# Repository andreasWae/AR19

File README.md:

# AR19
Repository inntil videre

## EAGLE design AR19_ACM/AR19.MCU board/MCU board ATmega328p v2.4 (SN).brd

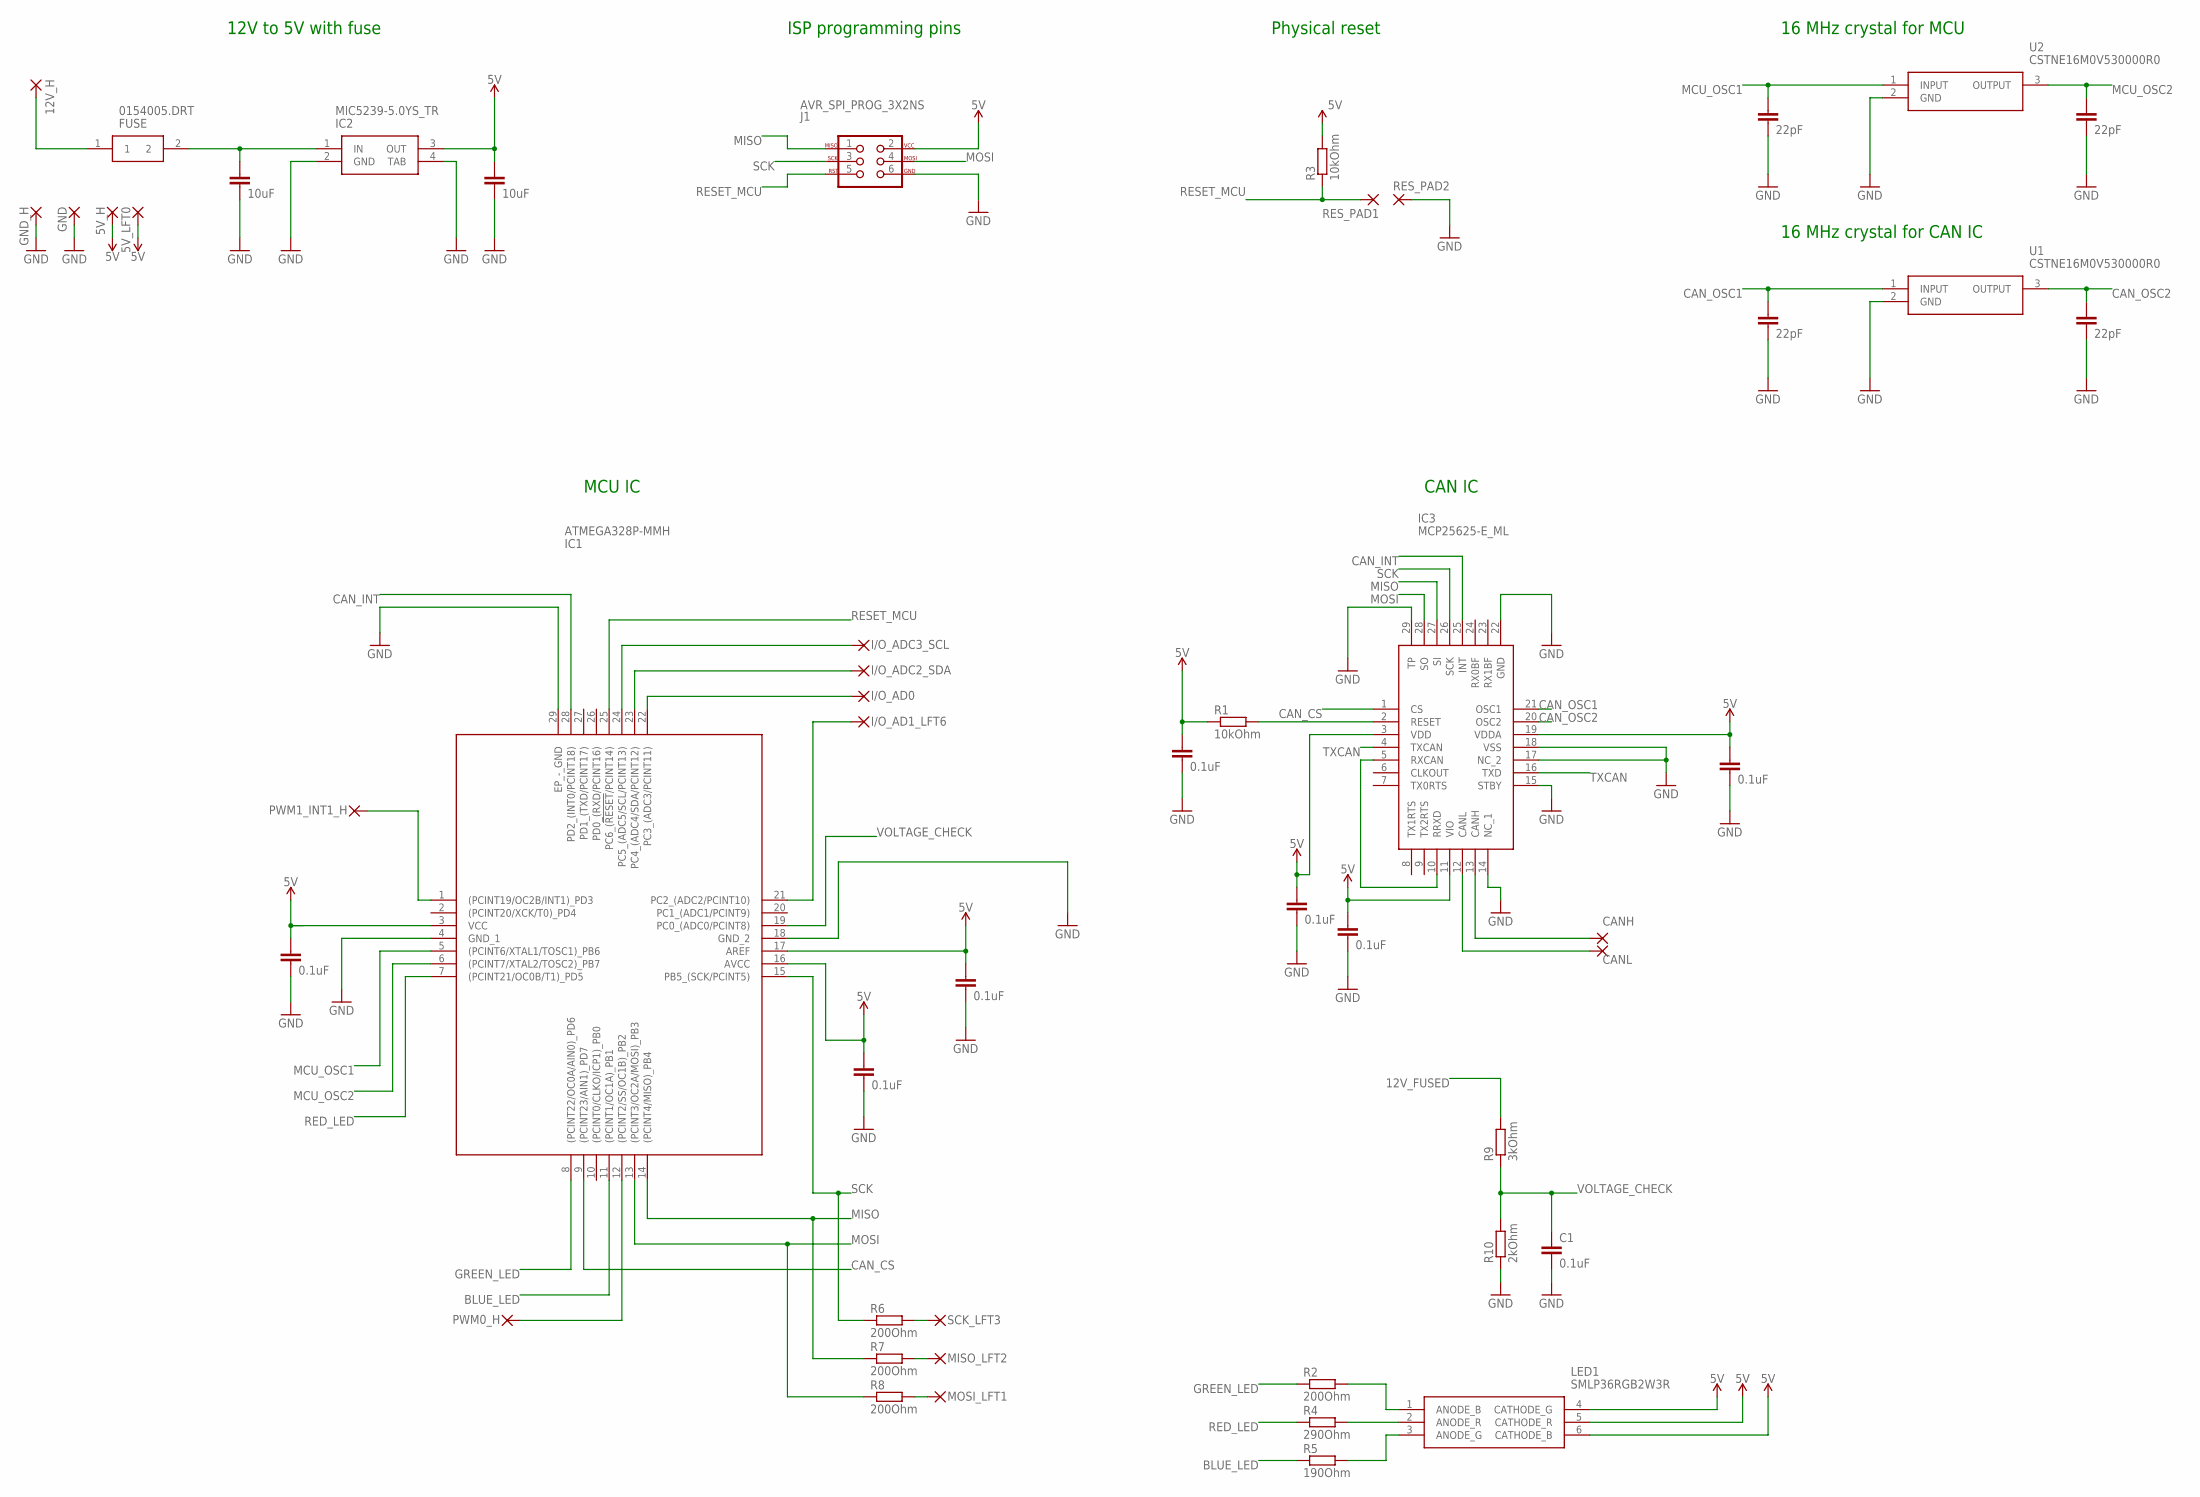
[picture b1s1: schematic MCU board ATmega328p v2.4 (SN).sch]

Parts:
5V: 5V_H; 2,15/1,0
5V1: 5V_LFT0; 2,15/1,0
12V_H: 12V; 2,15/1,0
C1, C6, C7, C8, C12, C13, C16, C17: 0.1uF; C0603
C2, C3, C5, C9: 22pF; C0603
C10, C11: 10uF; C0603
CANH: I/O_CANH_H; 2,15/1,0
CANL: I/O_CANH_H; 2,15/1,0
FUSE: 0154005.DRT; 0154001.DRT
GND: GND_H; 2,15/1,0
GND30_H: GND; 2,15/1,0
I/O_AD0: I/O_AD0_LFT7; 2,15/1,0
I/O_AD1: I/O_AD1_LFT6; 2,15/1,0
I/O_ADC2_SDA: I/O_ADC2_SDA_LFT5; 2,15/1,0
I/O_ADC3_SCL: I/O_ADC3_SCL_LFT4; 2,15/1,0
IC1: ATMEGA328P-MMH; QFN45P400X400X100-29N
IC2: MIC5239-5.0YS_TR; SOT230P700X170-4N
IC3: MCP25625-E_ML; QFN65P600X600X100-29N
J1: AVR_SPI_PROG_3X2NS; 2X3-NS
LED1: SMLP36RGB2W3R; ROHM-1510-(0604)
MISO: MISO_LFT2; 2,15/1,0
MOSI: MOSI_LFT1; 2,15/1,0
PWM0_H: PWM0; 2,15/1,0
PWM1_INT1_H: PWM0_INT; 2,15/1,0
R1, R3: 10kOhm; R0603
R2, R6, R7, R8: 200Ohm; R0603
R4: 290Ohm; R0603
R5: 190Ohm; R0603
R9: 3kOhm; R0603
R10: 2kOhm; R0603
RES_PAD1: RES_PAD; SMD1,27-2,54
RES_PAD2: RES_PAD2; SMD1,27-2,54
SCK: SCK_LFT3; 2,15/1,0
U1, U2: CSTNE16M0V530000R0

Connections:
5V: 5V.1, 5V1.1, C6.1, C7.1, C8.1, C11.1, C12.1, C13.1, C16.1, C17.1, IC1.3 (VCC), IC1.16 (AVCC), IC1.17 (AREF), IC2.3 (OUT), IC3.3 (VDD), IC3.11 (VIO), IC3.19 (VDDA), J1.2, LED1.4 (CATHODE_G), LED1.5 (CATHODE_R), LED1.6 (CATHODE_B), R1.1, R3.2
12V_FUSED: C10.1, FUSE.2, IC2.1 (IN), R9.2
12V_UNFUSED: 12V_H.1, FUSE.1
BLUE_LED: IC1.11 ((PCINT1/OC1A)_PB1), R5.1
CANH: CANH.1, IC3.13 (CANH)
CANL: CANL.1, IC3.12 (CANL)
CAN_CS: IC1.9 ((PCINT23/AIN1)_PD7), IC3.1 (CS)
CAN_INT: IC1.28 (PD2_(INT0/PCINT18)), IC3.25 (INT)
CAN_OSC1: C5.1, IC3.21 (OSC1), U1.1 (INPUT)
CAN_OSC2: C2.1, IC3.20 (OSC2), U1.3 (OUTPUT)
GND: C1.2, C2.2, C3.2, C5.2, C6.2, C7.2, C8.2, C9.2, C10.2, C11.2, C12.2, C13.2, C16.2, C17.2, GND.1, GND30_H.1, IC1.4 (GND_1), IC1.18 (GND_2), IC1.29 (EP_-_GND), IC2.2 (GND), IC2.4 (TAB), IC3.14 (NC_1), IC3.15 (STBY), IC3.17 (NC_2), IC3.18 (VSS), IC3.22 (GND), IC3.29 (TP), J1.6, R10.1, RES_PAD2.1, U1.2 (GND), U2.2 (GND)
GREEN_LED: IC1.8 ((PCINT22/OC0A/AIN0)_PD6), R2.1
I/OAD0: I/O_AD0.1, IC1.22 (PC3_(ADC3/PCINT11))
I/OADC2: I/O_ADC2_SDA.1, IC1.23 (PC4_(ADC4/SDA/PCINT12))
I/O_ADC3: I/O_ADC3_SCL.1, IC1.24 (PC5_(ADC5/SCL/PCINT13))
I/O_D2_INT: IC1.1 ((PCINT19/OC2B/INT1)_PD3), PWM1_INT1_H.1
MCU_OSC1: C3.1, IC1.5 ((PCINT6/XTAL1/TOSC1)_PB6), U2.1 (INPUT)
MCU_OSC2: C9.1, IC1.6 ((PCINT7/XTAL2/TOSC2)_PB7), U2.3 (OUTPUT)
MISO: IC1.14 ((PCINT4/MISO)_PB4), IC3.27 (SI), J1.1, R7.1
MOSI: IC1.13 ((PCINT3/OC2A/MOSI)_PB3), IC3.28 (SO), J1.4, R8.1
unnamed: IC3.2 (RESET), R1.2
unnamed: IC1.12 ((PCINT2/SS/OC1B)_PB2), PWM0_H.1
unnamed: I/O_AD1.1, IC1.21 (PC2_(ADC2/PCINT10))
unnamed: LED1.1 (ANODE_B), R2.2
unnamed: LED1.2 (ANODE_R), R4.2
unnamed: LED1.3 (ANODE_G), R5.2
unnamed: R6.2, SCK.1
unnamed: MISO.1, R7.2
unnamed: MOSI.1, R8.2
RED_LED: IC1.7 ((PCINT21/OC0B/T1)_PD5), R4.1
RESET_MCU: IC1.25 (PC6_(!RESET!/PCINT14)), J1.5, R3.1, RES_PAD1.1
RXCAN: IC3.5 (RXCAN), IC3.10 (RRXD)
SCK: IC1.15 (PB5_(SCK/PCINT5)), IC3.26 (SCK), J1.3, R6.1
TXCAN: IC3.4 (TXCAN), IC3.16 (TXD)
VOLTAGE_CHECK: C1.1, IC1.19 (PC0_(ADC0/PCINT8)), R9.1, R10.2

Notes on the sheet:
12V to 5V with fuse
ISP programming pins
Physical reset
16 MHz crystal for MCU
16 MHz crystal for CAN IC
CAN IC
MCU IC

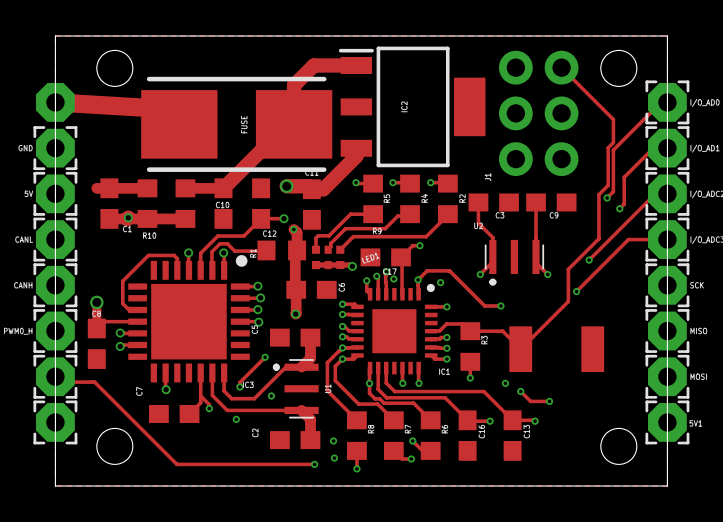
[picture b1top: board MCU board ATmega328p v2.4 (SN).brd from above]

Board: 4 copper layers, 34.0 x 25.0 mm, 50 parts (1 on the bottom side), 35 nets.

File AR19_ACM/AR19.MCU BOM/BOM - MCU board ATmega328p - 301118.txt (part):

Partlist exported from C:/Users/Nylund/Documents/Align Racing/AR19/PCB_Designs/GitKraken/AR19/ACM - Align CAN-bus Module/AR19.MCU board/MCU board ATmega328p v2.4.sch at 30-Nov-18 16:28

Part          Value              Device             Package               Description                                                                                                                                       ALLIED_NUMBER ALLIED_PRICE-STOCK                                                         ARROW_PART_NUMBER  ARROW_PRICE-STOCK                                                         DESCRIPTION                                                                                                                                       HEIGHT MANUFACTURER_NAME  MANUFACTURER_PART_NUMBER RS_PART_NUMBER RS_PRICE-STOCK                                  SPICEMODEL SPICEPREFIX
12V           12V                2,54/1,0           2,54/1,0              THROUGH-HOLE PAD                                                                                                                                                                                                                                                                                                                                                                                                                                                                                                                                                                                                                  
C1            0.1uF              CC0603             C0603                 CAPACITOR, European symbol                                                                                                                                                                                                                                                                                                                                                                                                                                                                                                                                                                                  NONE       C          
C2            22pF               CC0603             C0603                 CAPACITOR, European symbol                                                                                                                                                                                                                                                                                                                                                                                                                                                                                                                                                                                  NONE       C          
C3            22pF               CC0603             C0603                 CAPACITOR, European symbol                                                                                                                                                                                                                                                                                                                                                                                                                                                                                                                                                                                  NONE       C          
C5            22pF               CC0603             C0603                 CAPACITOR, European symbol                                                                                                                                                                                                                                                                                                                                                                                                                                                                                                                                                                                  NONE       C          
C6            0.1uF              CC0603             C0603                 CAPACITOR, European symbol                                                                                                                                                                                                                                                                                                                                                                                                                                                                                                                                                                                  NONE       C          
C7            0.1uF              CC0603             C0603                 CAPACITOR, European symbol                                                                                                                                                                                                                                                                                                                                                                                                                                                                                                                                                                                  NONE       C          
C8            0.1uF              CC0603             C0603                 CAPACITOR, European symbol                                                                                                                                                                                                                                                                                                                                                                                                                                                                                                                                                                                  NONE       C          
C9            22pF               CC0603             C0603                 CAPACITOR, European symbol                                                                                                                                                                                                                                                                                                                                                                                                                                                                                                                                                                                  NONE       C          
C10           10uF               CC0603             C0603                 CAPACITOR, European symbol                                                                                                                                                                                                                                                                                                                                                                                                                                                                                                                                                                                  NONE       C          
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
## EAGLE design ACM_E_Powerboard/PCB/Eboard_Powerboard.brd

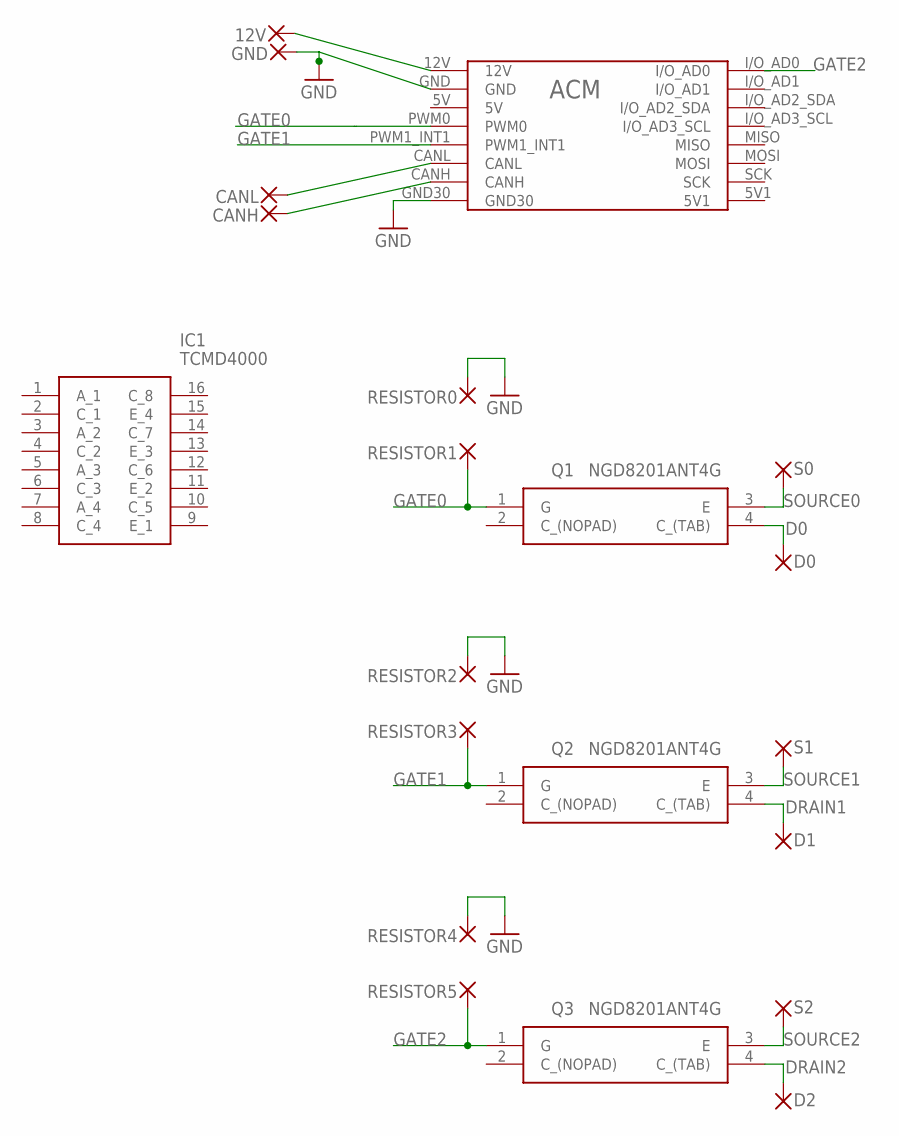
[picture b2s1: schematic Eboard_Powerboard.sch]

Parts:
12V: 2,15/1,0
CANH: 2,15/1,0
CANL: 2,15/1,0
D0, D1, D2: 2,54/1,0
GND: 2,15/1,0
IC1: TCMD4000; SOIC127P695X210-16N
Q1, Q2, Q3: NGD8201ANT4G; TO229P990X238-4N
RESISTOR0, RESISTOR1, RESISTOR2, RESISTOR3, RESISTOR4, RESISTOR5: 2,15/1,0
S0, S1, S2: 2,54/1,0
U$1: ACM_CASTELLATED; ACM_CAS_FP

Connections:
D0: D0.1, Q1.4 (C_(TAB))
DRAIN1: D1.1, Q2.4 (C_(TAB))
DRAIN2: D2.1, Q3.4 (C_(TAB))
GATE0: Q1.1 (G), RESISTOR1.1, U$1.PWM0
GATE1: Q2.1 (G), RESISTOR3.1, U$1.PWM1_INT1
GATE2: Q3.1 (G), RESISTOR5.1, U$1.I/O_AD0
GND: GND.1, RESISTOR0.1, RESISTOR2.1, RESISTOR4.1, U$1.GND, U$1.GND30
unnamed: 12V.1, U$1.12V
unnamed: CANL.1, U$1.CANL
unnamed: CANH.1, U$1.CANH
SOURCE0: Q1.3 (E), S0.1
SOURCE1: Q2.3 (E), S1.1
SOURCE2: Q3.3 (E), S2.1

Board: 2 copper layers, 21 parts (2 on the bottom side), 13 nets, no tracks yet.

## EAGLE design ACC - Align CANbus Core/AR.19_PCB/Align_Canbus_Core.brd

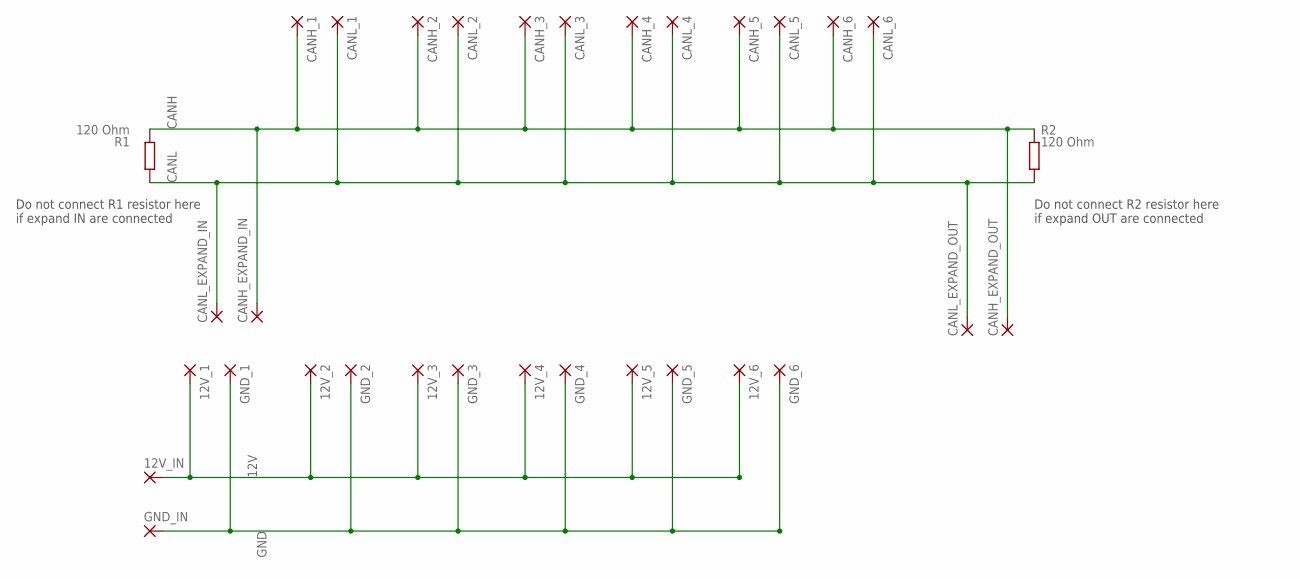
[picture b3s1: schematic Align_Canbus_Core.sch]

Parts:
12V_1, 12V_2, 12V_3, 12V_4, 12V_5, 12V_6: 2,15/1,0
12V_IN: 3,81/1,4
CANH_1, CANH_2, CANH_3, CANH_4, CANH_5, CANH_6: 2,15/1,0
CANH_EXPAND_IN: 2,54/1,0
CANH_EXPAND_OUT: 2,54/1,0
CANL_1, CANL_2, CANL_3, CANL_4, CANL_5, CANL_6: 2,15/1,0
CANL_EXPAND_IN: 2,54/1,0
CANL_EXPAND_OUT: 2,54/1,0
GND_1, GND_2, GND_3, GND_4, GND_5, GND_6: 2,15/1,0
GND_IN: 3,81/1,4
R1, R2: 120 Ohm; R0603

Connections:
12V: 12V_6.1, 12V_IN.1
CANH: CANH_1.1, CANH_2.1, CANH_3.1, CANH_4.1, CANH_5.1, CANH_6.1, CANH_EXPAND_IN.1, CANH_EXPAND_OUT.1, R1.2, R2.1
CANH1: 12V_1.1, 12V_2.1, 12V_3.1, 12V_5.1
CANL: CANL_1.1, CANL_2.1, CANL_3.1, CANL_4.1, CANL_5.1, CANL_6.1, CANL_EXPAND_IN.1, CANL_EXPAND_OUT.1, R1.1, R2.2
CANL1: GND_1.1, GND_2.1, GND_3.1, GND_5.1
GND: GND_6.1, GND_IN.1

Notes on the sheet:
Do not connect R1 resistor here if expand IN are connected
Do not connect R2 resistor here if expand OUT are connected

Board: 2 copper layers, 32 parts (0 on the bottom side), 6 nets, no tracks yet.

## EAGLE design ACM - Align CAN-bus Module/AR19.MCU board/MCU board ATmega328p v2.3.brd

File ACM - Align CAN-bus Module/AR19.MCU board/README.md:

# PCB Board
## Layers:
- Top Layer: 5V + Signal
- Route #2 Layer: Signal 1
- Route #3 Layer: Signal 2
- Route #4 Layer: GND

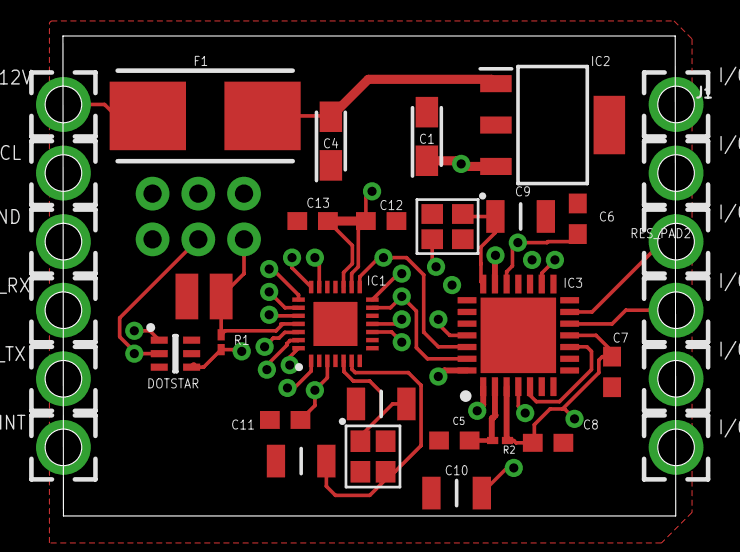
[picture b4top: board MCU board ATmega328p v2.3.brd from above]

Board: 4 copper layers, 34.0 x 26.7 mm, 37 parts (0 on the bottom side), 28 nets.

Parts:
12V: 2,54/2,0(HALFHOLE)H+V
C1, C4: 10uF; CAPPM3216X180N
C2, C3, C9, C10: 22pF; CAPC3216X229N
C5, C6, C7, C8, C11, C12, C13: 0.1uF; C0603
DOTSTAR: COM-14608; SON75P200X200X100-6N
F1: 0154005.DRT; 0154001.DRT
GND: 2,54/2,0(HALFHOLE)H+V
I/O_AD1, I/O_AD2, I/O_AD3, I/O_AD4_SDA, I/O_AD5_SCL: 2,54/2,0(HALFHOLE)H+V
I/O_CANH: 2,54/2,0(HALFHOLE)H+V
I/O_CANL: 2,54/2,0(HALFHOLE)H+V
I/O_D0_RX, I/O_D1_TX, I/O_D2_INT: 2,54/2,0(HALFHOLE)H+V
IC1: ATMEGA328P-MMH; QFN45P400X400X100-29N
IC2: MIC5239-5.0YS_TR; SOT230P700X170-4N
IC3: MCP25625-E_ML; QFN65P600X600X100-29N
J1: AVR_SPI_PROG_3X2NS; 2X3-NS
R1, R2: 10KΩ; RESC0603X28N
RES_PAD1, RES_PAD2: SMD1,27-2,54
U$1, U$2: FA-20H

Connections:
5V: C1.1, C6.1, C7.1, C8.1, C11.1, C12.1, C13.1, DOTSTAR.4, IC1.3, IC1.16, IC1.17, IC2.3, IC3.3, IC3.11, IC3.19, J1.2, R1.2, R2.2
12V_FUSED: C4.2, F1.2, IC2.1
12V_UNFUSED: 12V.P$1, F1.1
CANH: I/O_CANH.P$1, IC3.13
CANL: I/O_CANL.P$1, IC3.12
CAN_CS: IC1.11, IC3.1
CAN_INIT: IC1.28, IC3.25
CAN_OSC1: C9.2, IC3.21, U$1.1
CAN_OSC2: C10.2, IC3.20, U$1.3
DOTS_CS: DOTSTAR.1, IC1.10
GND: C1.2, C2.1, C3.1, C4.1, C5.2, C6.2, C7.2, C8.2, C9.1, C10.1, C11.2, C12.2, C13.2, DOTSTAR.3, GND.P$1, IC1.4, IC1.18, IC1.29, IC2.2, IC2.4, IC3.14, IC3.15, IC3.17, IC3.18, IC3.22, J1.6, RES_PAD2.1
I/O_AD1: I/O_AD1.P$1, IC1.20
I/O_AD2: I/O_AD2.P$1, IC1.21
I/O_AD3: I/O_AD3.P$1, IC1.22
I/O_AD4_SCL: I/O_AD4_SDA.P$1, IC1.23
I/O_AD5_SCL: I/O_AD5_SCL.P$1, IC1.24
I/O_D0_RX: I/O_D0_RX.P$1, IC1.26
I/O_D1_TX: I/O_D1_TX.P$1, IC1.27
I/O_D2_INT: I/O_D2_INT.P$1, IC1.1
MCP_RESET: C5.1, IC3.2, R2.1
MCU_OSC1: C2.2, IC1.5, U$2.1
MCU_OSC2: C3.2, IC1.6, U$2.3
MISO: IC1.14, IC3.28, J1.1
MOSI: IC1.13, IC3.27, J1.4
RESET_MCU: IC1.25, J1.5, R1.1, RES_PAD1.1
RXCAN: IC3.5, IC3.10
SCK: DOTSTAR.2, IC1.15, IC3.26, J1.3
TXCAN: IC3.4, IC3.16

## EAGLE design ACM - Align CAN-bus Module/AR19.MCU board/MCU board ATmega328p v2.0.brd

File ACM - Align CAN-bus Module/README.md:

# ACM - Align CAN-bus Module
TBA

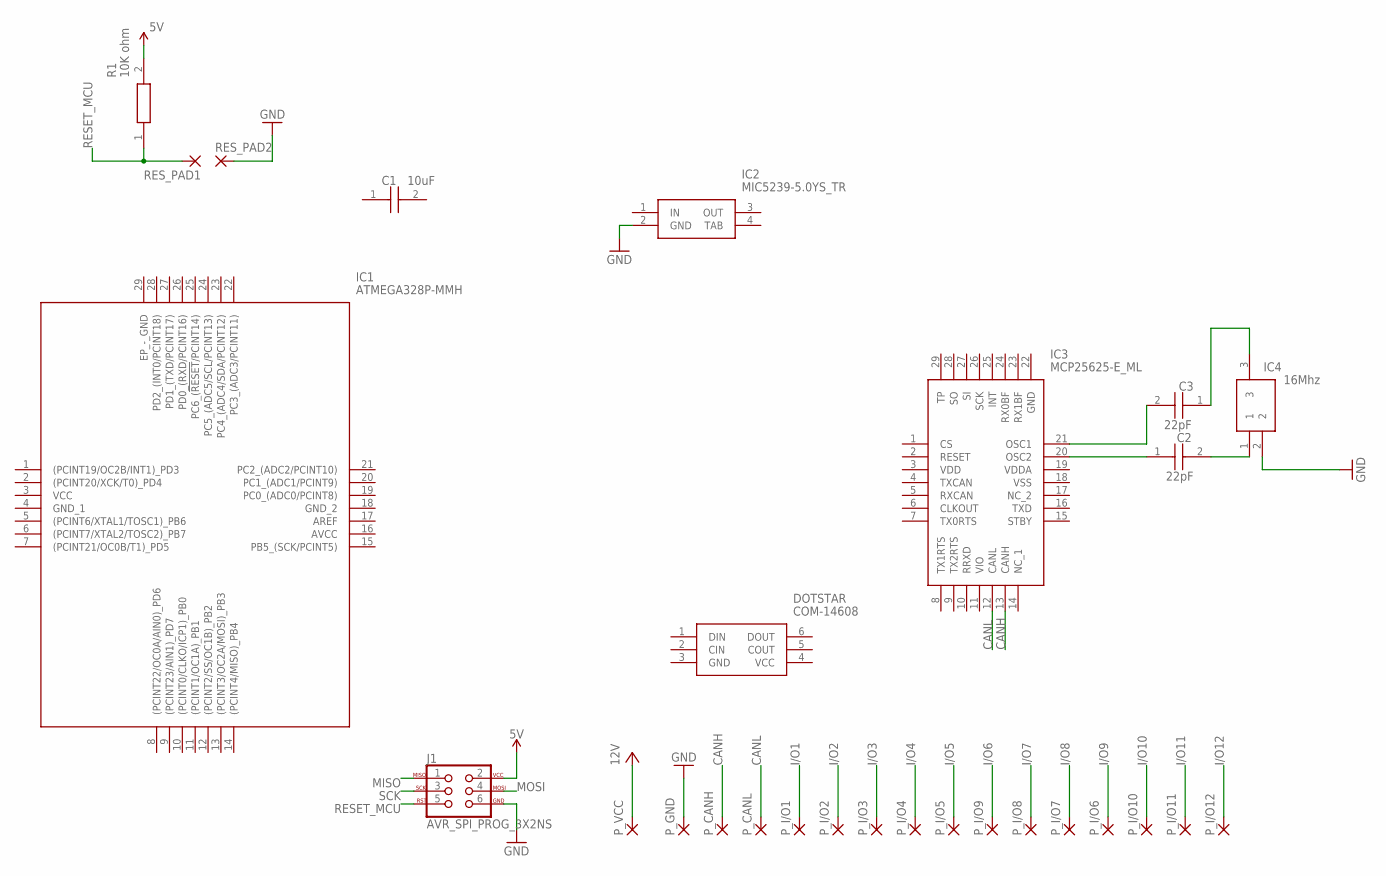
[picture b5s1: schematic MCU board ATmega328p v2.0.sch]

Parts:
C1: 10uF; CAPPM3216X180N
C2, C3: 22pF; CAPC3216X229N
DOTSTAR: COM-14608; SON75P200X200X100-6N
IC1: ATMEGA328P-MMH; QFN45P400X400X100-29N
IC2: MIC5239-5.0YS_TR; SOT230P700X170-4N
IC3: MCP25625-E_ML; QFN65P600X600X100-29N
IC4: 16Mhz; CSTCE16M0V13C99R0
J1: AVR_SPI_PROG_3X2NS; 2X3-NS
P_CANH: 2,15/1,0
P_CANL: 2,15/1,0
P_GND: 2,15/1,0
P_I/O1, P_I/O2, P_I/O3, P_I/O4, P_I/O5, P_I/O6, P_I/O7, P_I/O8, P_I/O9, P_I/O10, P_I/O11, P_I/O12: 2,15/1,0
P_VCC: 2,15/1,0
R1: 10K ohm; RESC0603X28N
RES_PAD1, RES_PAD2: SMD2; SMD1,27-2,54

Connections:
5V: J1.2, R1.2
CANH: IC3.13 (CANH), P_CANH.1
CANL: IC3.12 (CANL), P_CANL.1
GND: IC2.2 (GND), IC3.22 (GND), IC4.2, J1.6, P_GND.1, RES_PAD2.1
I/O1: P_I/O1.1
I/O2: P_I/O2.1
I/O3: P_I/O3.1
I/O4: P_I/O4.1
I/O5: P_I/O5.1
I/O6: P_I/O9.1
I/O7: P_I/O8.1
I/O8: P_I/O7.1
I/O9: P_I/O6.1
I/O10: P_I/O10.1
I/O11: P_I/O11.1
I/O12: P_I/O12.1
MISO: J1.1
MOSI: J1.4
unnamed: C3.2, IC4.1
unnamed: C3.1, IC3.20 (OSC2)
unnamed: C2.2, IC3.21 (OSC1)
unnamed: C2.1, IC4.3
RESET_MCU: J1.5, R1.1, RES_PAD1.1
SCK: J1.3
VCC: P_VCC.1
VDD: IC3.3 (VDD)
VDDA: IC3.19 (VDDA)
VSS: IC3.18 (VSS)

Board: 2 copper layers, 28 parts (0 on the bottom side), 9 nets, no tracks yet.

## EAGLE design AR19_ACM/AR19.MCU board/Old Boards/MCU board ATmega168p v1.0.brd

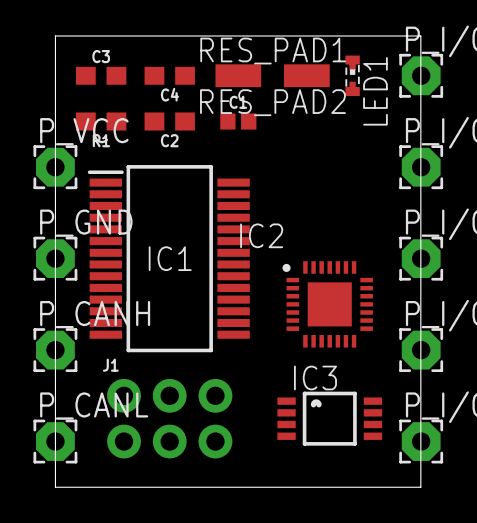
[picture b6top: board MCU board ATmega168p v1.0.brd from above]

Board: 2 copper layers, 20.3 x 25.1 mm, 21 parts (0 on the bottom side), 13 nets, no tracks yet.

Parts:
C1: 0.1uF; 0402
C2: 10uF; 0603
C3, C4: 22pF; 0603
IC1: MCP25625-E_SS; SOP65P780X200-28N
IC2: ATMEGA328P-MMH; QFN45P400X400X100-29N
IC3: LM2936MM-5.0; MINI-SO8
J1: AVR_SPI_PROG_3X2NS; 2X3-NS
LED1: SMARTLED-TTW
P_CANH: 2,15/1,0
P_CANL: 2,15/1,0
P_GND: 2,15/1,0
P_I/O1, P_I/O2, P_I/O3, P_I/O4, P_I/O5: 2,15/1,0
P_VCC: 2,15/1,0
R1: 10k; 0603
RES_PAD1, RES_PAD2: SMD1,27-2,54

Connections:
5V: C2.1, IC1.1, IC1.19, IC1.27, IC3.1, J1.2, R1.2
12V: C1.1, IC3.8
CANH: IC1.4, P_CANH.1
CANL: IC1.3, P_CANL.1
GND: C1.2, C2.2, C3.1, C4.1, IC1.5, IC1.10, IC1.26, IC3.7, J1.6, P_GND.1, RES_PAD2.1
MISO: IC1.16, J1.1
MOSI: IC1.15, J1.4
unnamed: C4.2, IC1.9
unnamed: C3.2, IC1.8
unnamed: IC1.21, IC1.28
unnamed: IC1.20, IC1.24
RESET_MCU: J1.5, R1.1, RES_PAD1.1
SCK: IC1.14, J1.3

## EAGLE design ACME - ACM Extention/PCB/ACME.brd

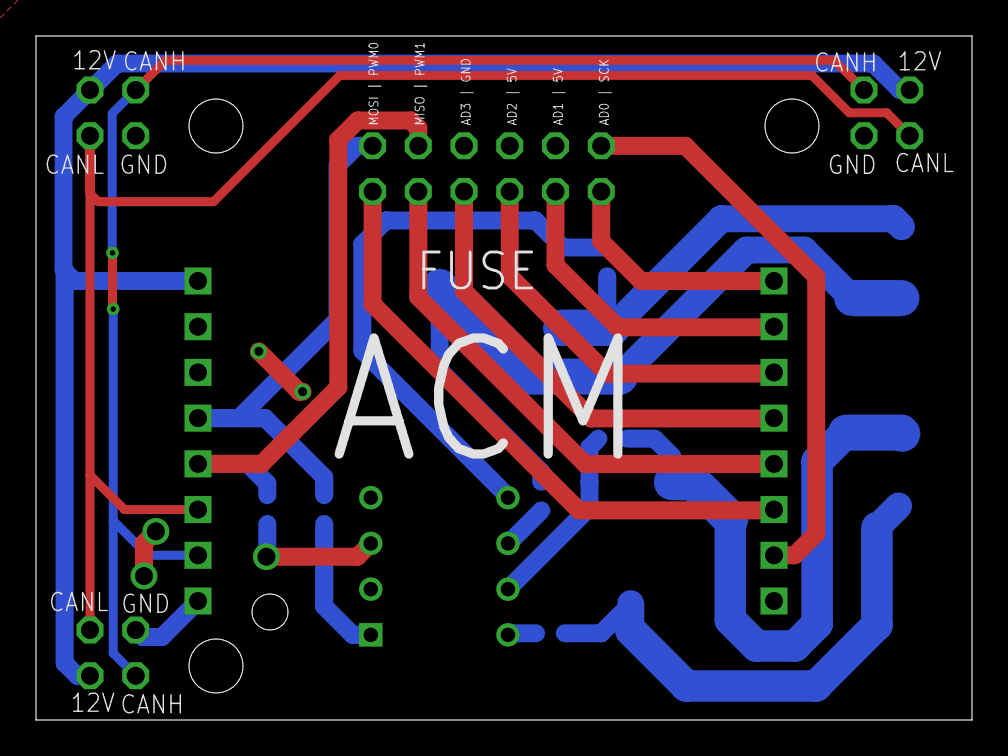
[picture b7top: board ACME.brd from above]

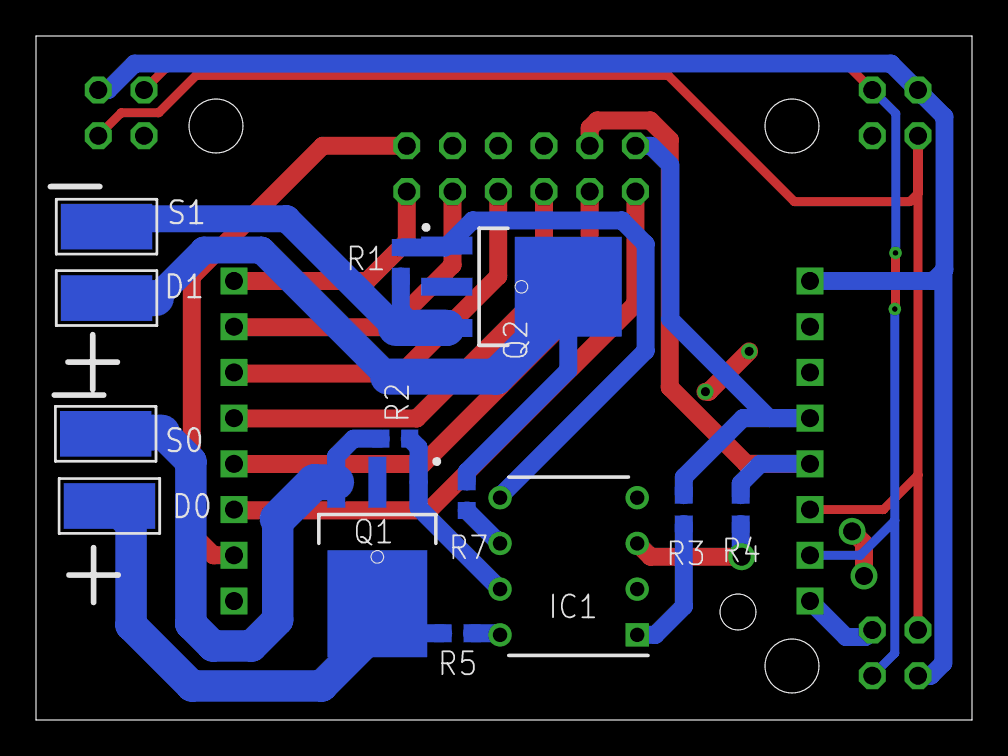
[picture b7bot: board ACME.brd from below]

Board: 2 copper layers, 52.0 x 38.0 mm, 18 parts (13 on the bottom side), 24 nets.

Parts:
D0, D1: 5-2,5
IC1: Optocoupler DIP; DIP762W60P254L966H485Q8N
Q1, Q2: TO229P990X238-4N
R1, R2: RESC1608X55N
R3, R4: 200 Ohm; RESC1608X55N
R5, R7: 1K Ohm; RESC1608X55N
S0, S1: 5-2,5
U$1: ACM_CASTELLATED; ACM_CAS_FP
U$2, U$3, U$4, U$5: 16P_CONNECTOR; 16P_CONNECTOR_FP

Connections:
5V: U$1.5V1_P, U$1.5V_P, U$2.4, U$2.5
12V: U$1.12V_P, U$3.1, U$4.2, U$5.3
AD0: U$1.I/O_AD0_P, U$2.12
AD1: U$1.I/O_AD1_P, U$2.11
AD2: U$1.I/O_AD2_SDA_P, U$2.10
AD3: U$1.I/O_AD3_SCL_P, U$2.9
CANH: U$1.CANH_P, U$3.2, U$4.1, U$5.4
CANL: U$1.CANL_P, U$3.3, U$4.4, U$5.1
DRAIN0: D0.1, Q1.4, R5.2
DRAIN1: D1.1, Q2.4, R7.2
GATE0: IC1.7, Q1.1, R2.1
GATE1: IC1.5, Q2.1, R1.1
GND: IC1.2, IC1.4, U$1.GND0_P, U$1.GND1_P, U$2.3, U$3.4, U$4.3, U$5.2
MISO: U$1.MISO_P, U$2.8
MOSI: U$1.MOSI_P, U$2.7
unnamed: IC1.1, R3.1
unnamed: IC1.3, R4.1
unnamed: IC1.8, R5.1
unnamed: IC1.6, R7.1
PWM0: R3.2, U$1.PWM0_P, U$2.1
PWM1: R4.2, U$1.PWM1_INT1_P, U$2.2
SCK: U$1.SCK_P, U$2.6
SOURCE0: Q1.3, R2.2, S0.1
SOURCE1: Q2.3, R1.2, S1.1

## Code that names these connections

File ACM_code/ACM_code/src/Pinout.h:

//
//  AR19 - Pinout.h
//  University of Agder - 2018
//  Group: Simon Nylund and Andreas Wæhle
//
//  File: Pinout.h
//  Control_V1.0
//  Descrption: Initialize all used I/O pins.
//
//  Created by Andreas Wæhle on 25/11/2018.
//  

#ifndef Pinout_h
#define Pinout_h


//Usable INPUTS/OUTPUTS


const uint8_t PWM0          = 10;   // PB2; PWM pin or chip select for MCU if using SPI
const uint8_t PWM1_INT1     = 3;    // PD3; INT1 input pin or PWM pin
const uint8_t ADC0          = A3;   // PC3; Analog/digital pin       
const uint8_t ADC1          = A2;   // PC2; Analog/digital pin
const uint8_t ADC2_SDA      = A4;   // PC4; SDA pin for I2C or analog/digital pin
const uint8_t ADC3_SCL      = A5;   // PC5; SCL pin for I2C or analog/digital pin
const uint8_t MISO          = 11;   // PB4; MISO pin for SPI, DO NO USE WITHOUT SERIES RESISTOR
const uint8_t MOSI          = 12;   // PB3; MOSI pin for SPI, DO NO USE WITHOUT SERIES RESISTOR
const uint8_t SCK           = 13;   // PB5; Clock pin for SPI, DO NOT USE WITHOUT SERIES RESISTOER 

//OUTPUTS

const uint8_t RED_LED       = 5;    // PD5; PWM output to red led in the RGB led
const uint8_t GREEN_LED     = 6;    // PD6; PWM output to green led in the RGB led
const uint8_t BLUE_LED      = 9;    // PB1; PWM output to blue led in the RGB led 

//INPUTS

const uint8_t VOLTAGE_CHECK = A0;   // PC0; Internal on board voltage check pin

#endif

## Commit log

2018-10-31 Add files via upload
    Images and libraires
2018-10-31 Add files via upload
    100/158
2018-10-31 Revert "Add files via upload"
    This reverts commit c378eaefde4d68ae9384862f75b5b84b92e21868.
2018-11-01 Endret litt på oppsett rundt MCP25625
2018-11-02 Oppdatering MCP-25625
2018-11-02 ADD INT MCU
2018-11-02 Added FA-20H Crystal
2018-11-02 Ryddet og la til den nye krystallen
2018-11-02 Pakket og klart
2018-11-03 Created BOM 031018
2018-11-03 Added: Google drive shortcut
2018-11-03 Added: Fuse Block (Littelfuse SMD fuse block)
2018-11-03 Exploded PCB Board
2018-11-03 Added: Orange Power LED with 500ohm resistor
2018-11-03 Board saved
2018-11-04 Added: Datasheets and capacitors to ATMEGA328p
2018-11-04 Removed: Extra CAN port and Tested Board routing
2018-11-04 Added: Libraries and images
2018-11-04 Added DRC and .SCH layout changes
2018-11-04 Added LDO PDF
2018-11-04 Finished .SCH v2.3
2018-11-04 Begynt å lage board
2018-11-04 Progress with tracing (40 Air-errors left), Change text size to 20
2018-11-04 Update Readme.md with layers.
2018-11-05 ADDED: Support for Half cut/castellated holes.
2018-11-05 Deleted AD0 and minor changes to board file
2018-11-05 Removed: Extra GND connections
2018-11-05 Everything connected except GND and 5V Plane
2018-11-05 Added: Ratsnest GND on Top and 4th Layer
2018-11-05 9 Airwire errors
2018-11-05 Fixed Airwire problems | Added: Connectet MISO Atmega with MCP
2018-11-07 Added: Order list image
2018-11-08 Added: Code folder and LED test code
2018-11-08 + SPI Priority | / 10K and 500Ohm to larger package | Smallest part 1206
2018-11-12 Updated BOM and SPI Priority
2018-11-13 New board
2018-11-17 Startet kode mappe
2018-11-22 Byttet I/O pins, 0603 imp smd størrelse. Mangler dotstar support
2018-11-25 Added: GND to FA-20H
2018-11-26 Added: CAN-Bus test code (Simon)
2018-11-29 Programkode endring mot ACM
2018-11-29 Added: Resonator lib
2018-11-29 Changes in schematic
2018-11-29 Added GND I/O pin XD
2018-11-30 Voltage divider resistor changed
2018-11-30 Added. PDFs
2018-11-30 BOM Updated
2018-11-30 Board creation SN og SW
2018-12-01 Added: 35x25mm ACM v.SN
2018-12-01 Removed all errors, except dimension errors.
2018-12-01 Created a new board REV. B 33x25mm Nice to look at!
2018-12-01 Small routing fixes (Non critical)
2018-12-02 Rerouted and moved components
2018-12-02 Added illustrations and reouted
2018-12-02 Small fixes
2018-12-06 Added: Images and Gerberoutput
2018-12-06 Added more images
2018-12-06 Fixing filesystem
2018-12-10 Created: ACM Library for other PCBs (Not Ready)
2018-12-10 Added images
2018-12-10 ACM Library ready
2018-12-11 Created Align CANbus Core (ACC)
2018-12-12 CANbus Core: Input and output expansion added
2018-12-15 Uplaod AW ACM version from early dec19
2018-12-15 Gotta stage it all - pokemon!
2018-12-15 Removed Align CANbus Core after discussion.
2018-12-16 Removed canbus core
2019-01-13 Created ACM rev. C
2019-01-14 Removed GND from Oscillator. Added new ACM library
2019-01-15 Moved PWM pins away from under oscillator
2019-01-19 Added: Powerboard
2019-01-24 Powerboard RDY
2019-01-24 Added Falstad simulation
2019-01-25 Adder gerberfile
2019-02-01 Added: ACM Function test code
2019-02-01 Created ACM core code for onboard LED
2019-02-02 LED test update
2019-02-02 Added: Pin Library
2019-02-03 Added: Test code
2019-02-05 Added AR-Brakelight_v3
2019-02-05 Brakelight - Fixed positions ready for tracing
2019-02-05 Brakelight only stubs left
2019-02-06 Added: ACM hub library
2019-02-13 Change: ACM_Hub
2019-02-13 Ready: Brakelight PCB
2019-02-13 Fixed: Brakelight Silkscreen and generated Gerber.
2019-02-13 Brakelight check, and clear for production...
2019-02-25 ACM_Hub_Progress
2019-02-28 ACM_Hub_Progress 2
2019-02-28 ACM_Hub (Hotswap) Ready
2019-02-28 ACM Hotswap ready for prduction
2019-03-02 Renamed to ACME (ACM Extension)
2019-03-03 New version of ACME
2019-03-04 Testcode update
2019-03-04 ACME: Changed PWM Routing for isolation
2019-03-04 ACME: Silkcreeen and copper pour settings for isolation
2019-03-04 ACME: Fixed DRC
2019-03-04 ACME: ACME Ready for production
2019-03-04 ACME: Generated STEP File
2019-03-18 ACME
2019-04-06 Created break light code
2019-04-06 Added metadata and pressure equation
2019-04-06 Added ACME Svhematic
2019-04-06 ACME fix
2019-04-12 Brakelight Code working
2019-04-14 Ryddet litt etter AR Standard
2019-05-03 Moved to official AR-19 Git

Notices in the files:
parts and their libraries:
SparkFun-Connectors: Licensing: Creative Commons ShareAlike 4.0 International - https://creativecommons.org/licenses/by-sa/4.0
